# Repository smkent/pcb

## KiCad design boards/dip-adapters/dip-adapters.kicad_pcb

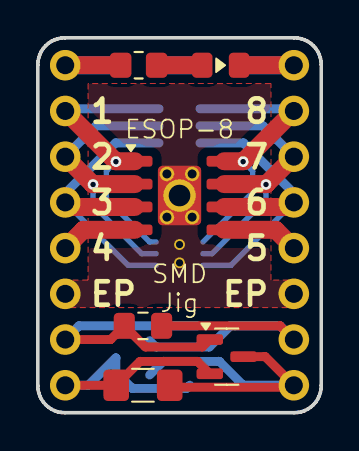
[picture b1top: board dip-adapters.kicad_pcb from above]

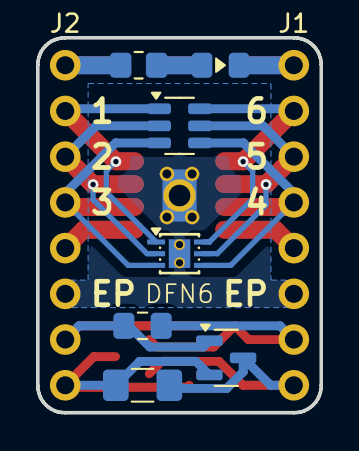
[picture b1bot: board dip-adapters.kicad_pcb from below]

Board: 2 copper layers, 15.7 x 20.8 mm, 15 parts (9 on the bottom side), 17 nets.

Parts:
C1, C2: C; C_0805_2012Metric_Pad1.18x1.45mm_HandSolder
F1, F2: Polyfuse; Fuse_1206_3216Metric_Pad1.42x1.75mm_HandSolder
J1, J2: Conn_01x08; PinHeader_1x08_P2.54mm_Vertical_simple
LED1, LED2: LED; LED_0805_2012Metric_Pad1.15x1.40mm_HandSolder_simple
Q1, Q2: AO3401A; SOT-23
R1, R2: 1K; R_0805_2012Metric_Pad1.20x1.40mm_HandSolder
U1: TP4056; SOIC-8-1EP_3.9x4.9mm_P1.27mm_EP2.41x3.3mm_ThermalVias_Custo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
U2: 1EDN7550B; SOT-23-6
U3: XB6366D; DFN-6_L2.0-W2.0-P0.65-BL-EP_ThermalVias_HandSolder

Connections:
1: J1.2, U1.1 (TEMP), U2.6 (OUT_SNK), U3.6 (VM)
2: J1.3, U1.2 (PROG), U2.5 (OUT_SRC), U3.5 (VM)
3: J1.4, U1.3 (GND), U2.4 (VDD), U3.4 (VM)
4: J1.5, U1.4 (VCC)
5: J2.5, U1.5 (BAT)
6: J2.4, U1.6 (~STDBY), U2.3 (IN+), U3.3 (GND)
7: J2.3, U1.7 (~CHRG), U2.2 (GND), U3.2 (GND)
8: J2.2, U1.8 (CE), U2.1 (IN-), U3.1 (VDD)
EP: J1.6, J2.6, U1.9 (EP), U3.7 (EP)
L7: C1.1, C2.1, J2.7, Q2.1 (G)
L8: F1.1, F2.1, J2.8, Q1.3 (D), Q2.2 (S)
unnamed: J1.1, LED2.1 (K), R2.1
unnamed: J2.1, LED1.1 (K), R1.1
unnamed: LED1.2 (A), R2.2
unnamed: LED2.2 (A), R1.2
R7: C1.2, C2.2, J1.7, Q1.1 (G)
R8: F1.2, F2.2, J1.8, Q1.2 (S), Q2.3 (D)

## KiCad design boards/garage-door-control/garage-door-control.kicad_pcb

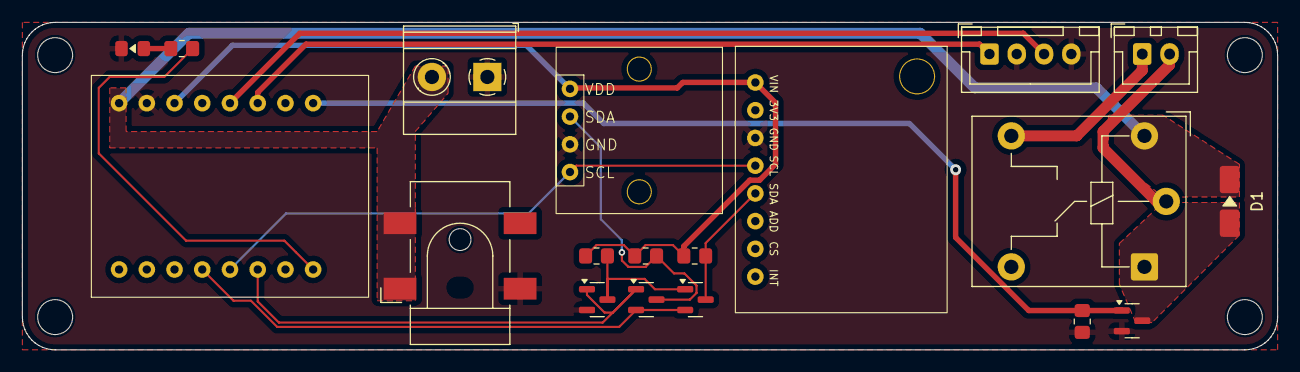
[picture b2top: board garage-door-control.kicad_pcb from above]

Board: 2 copper layers, 115.0 x 30.0 mm, 19 parts (0 on the bottom side), 17 nets.

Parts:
D1: SS34; D_SMA_simple
J1: Barrel_Jack_Switch; BarrelJack_CLIFF_FC681465S_SMT_Horizontal
J2: Conn_01x02; JST_XH_B2B-XH-A_1x02_P2.50mm_Vertical
J3: Conn_01x04_Socket; JST_XH_B4B-XH-A_1x04_P2.50mm_Vertical
J4: Conn_01x02; TerminalBlock_Phoenix_MKDS-1,5-2-5.08_1x02_P5.08mm_Horizont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
K1: Relay_SPDT; Relay_SPDT_Hongfa_HF3F-L-xx-1ZL1T
LED1: LED; LED_0805_2012Metric_Pad1.15x1.40mm_HandSolder_simple
Q1, Q2, Q3, Q4: BSS138; SOT-23
R1, R2, R3, R4, R5: 10K; R_0805_2012Metric_Pad1.20x1.40mm_HandSolder
U1: ESP32-C3-Super-Mini-Pins
U2: AHT20+BMP280
U3: ENS160+AHT2x

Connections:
+3V3: R3.2, R4.2, R5.2, U1.3V3, U2.1 (VDD), U3.1 (VIN)
+5V: D1.1 (K), J1.1, J4.2, K1.A2, U1.5V
BUS0_SDA: Q4.3 (D), R4.1, U2.2 (SDA)
BUS1_SDA: Q3.3 (D), R5.1, U3.5 (SDA)
DOOR_SENSE: J3.3, U1.3
GND: J1.3, J3.2, J3.4, J4.1, LED1.1 (K), Q1.2 (S), Q2.2 (S), R1.1, U1.G (Ground), U2.3 (GND), U3.3 (GND)
LED_STATUS: R2.2, U1.21
LOCK_SENSE: J3.1, U1.2
unnamed: LED1.2 (A), R2.1
unnamed: Q2.3 (D), Q3.1 (G), R3.1
RELAY_COIL: D1.2 (A), K1.A1, Q1.3 (D)
RELAY_CONTROL: Q1.1 (G), R1.2, U1.0
RELAY_SW_COMMON: J2.2, K1.11
RELAY_SW_NO: J2.1, K1.14
SCL: U1.9, U2.4 (SCL), U3.4 (SCL)
SDA: Q3.2 (S), Q4.2 (S), U1.8
SEL: Q2.1 (G), Q4.1 (G), U1.10

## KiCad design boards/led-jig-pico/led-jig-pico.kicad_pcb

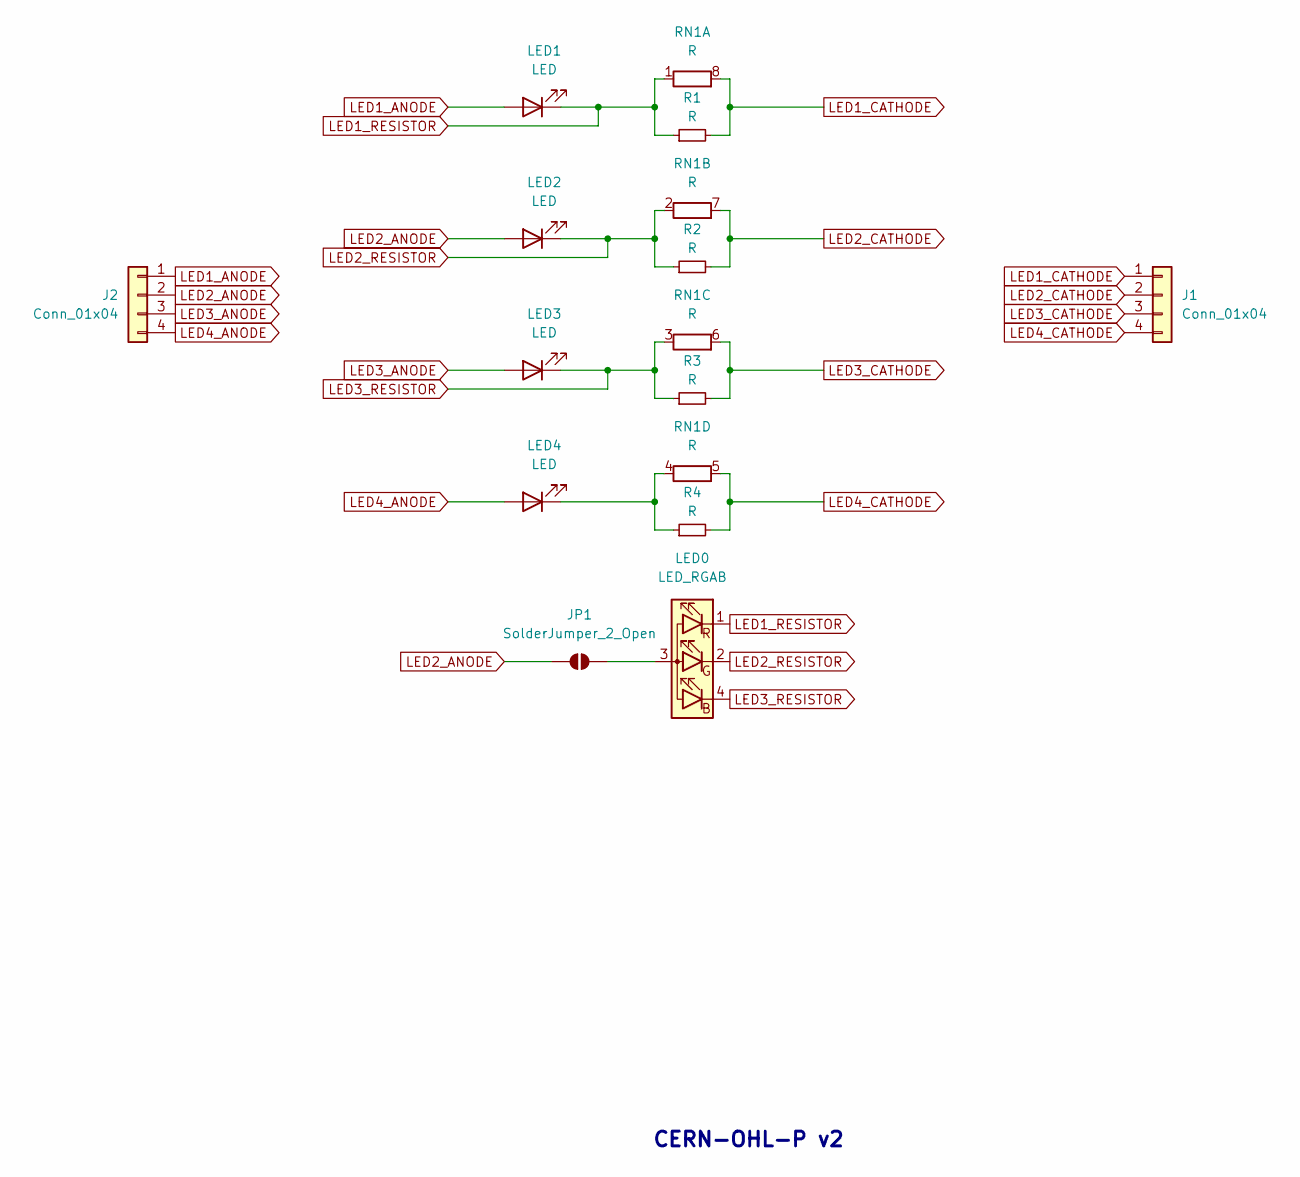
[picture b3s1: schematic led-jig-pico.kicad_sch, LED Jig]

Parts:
J1, J2: Conn_01x04; PinHeader_1x04_P2.54mm_Vertical_simple
JP1: SolderJumper_2_Open; SolderJumper-2_P1.3mm_Open_TrianglePad1.0x1.5mm
LED0: LED_RGAB; LED-ARRAY-SMD_4P-L2.0-W1.3-BR_HandSolder; LCSC Part C965848
LED1, LED2, LED3, LED4: LED; LED_0805_2012Metric_Pad1.15x1.40mm_HandSolder_simple
R1, R2, R3, R4: R; R_0805_2012Metric_Pad1.20x1.40mm_HandSolder
RN1: R; R_Array_Convex_4x0603

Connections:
LED1_ANODE: J2.1, LED1.2 (A)
LED1_CATHODE: J1.1, R1.2, RN1.8 (R1.2)
LED1_RESISTOR: LED0.1 (RK), LED1.1 (K), R1.1, RN1.1 (R1.1)
LED2_ANODE: J2.2, JP1.1 (A), LED2.2 (A)
LED2_CATHODE: J1.2, R2.2, RN1.7 (R2.2)
LED2_RESISTOR: LED0.2 (GK), LED2.1 (K), R2.1, RN1.2 (R2.1)
LED3_ANODE: J2.3, LED3.2 (A)
LED3_CATHODE: J1.3, R3.2, RN1.6 (R3.2)
LED3_RESISTOR: LED0.4 (BK), LED3.1 (K), R3.1, RN1.3 (R3.1)
LED4_ANODE: J2.4, LED4.2 (A)
LED4_CATHODE: J1.4, R4.2, RN1.5 (R4.2)
unnamed: JP1.2 (B), LED0.3 (A)
unnamed: LED4.1 (K), R4.1, RN1.4 (R4.1)

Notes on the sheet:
CERN-OHL-P v2

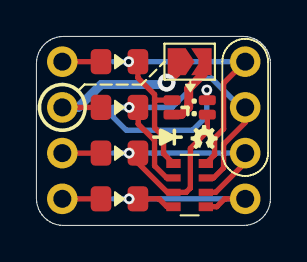
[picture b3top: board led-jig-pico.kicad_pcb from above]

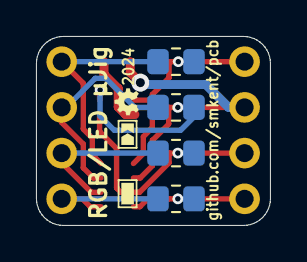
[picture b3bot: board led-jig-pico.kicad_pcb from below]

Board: 2 copper layers, 13.0 x 10.5 mm, 13 parts (6 on the bottom side), 13 nets.

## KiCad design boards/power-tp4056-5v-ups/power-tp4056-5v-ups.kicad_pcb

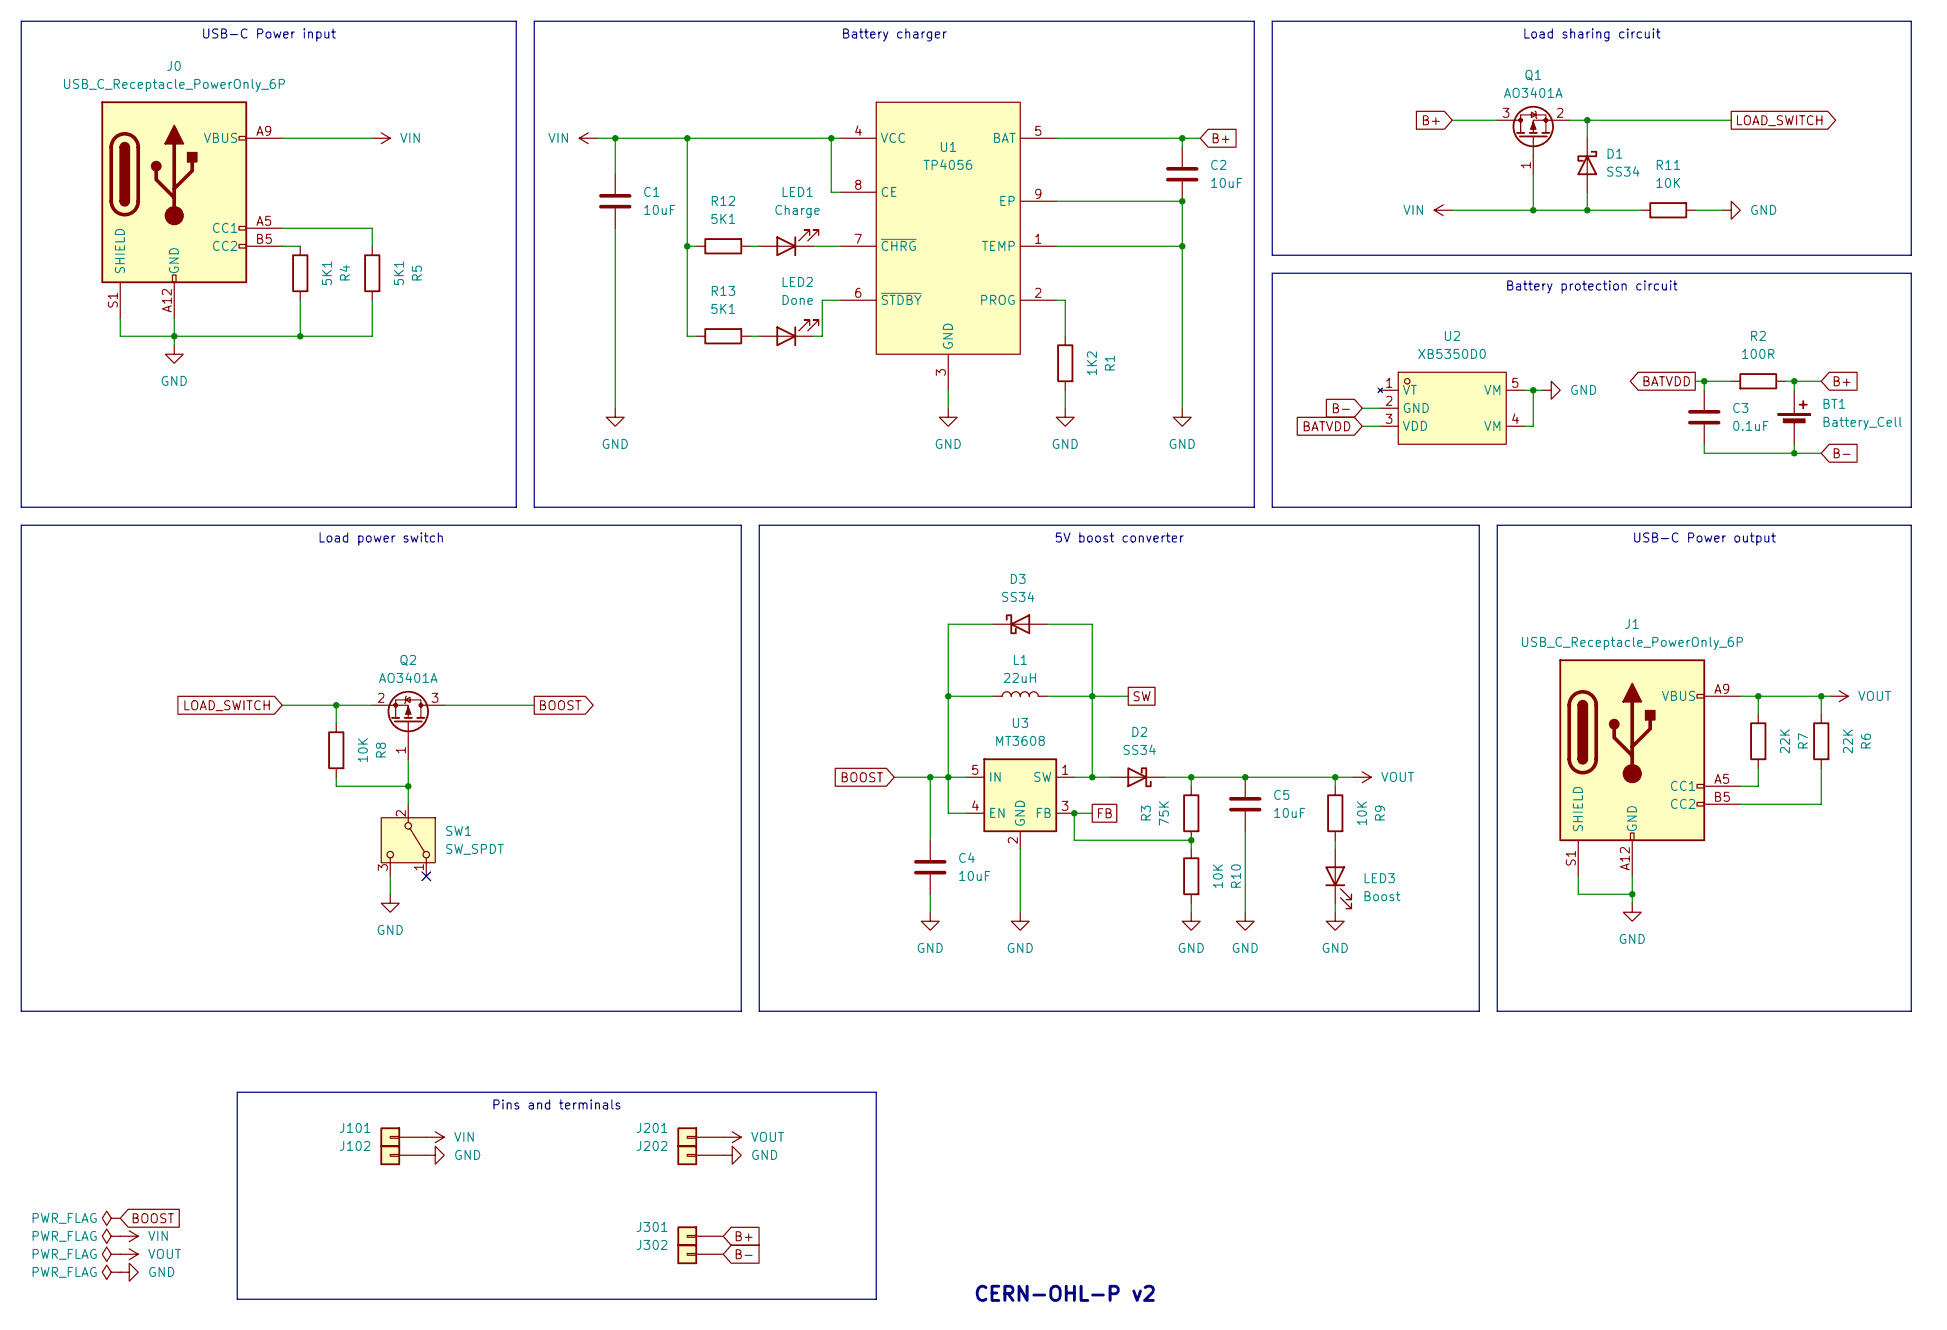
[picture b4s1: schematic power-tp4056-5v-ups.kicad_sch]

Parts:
BT1: Battery_Cell; JST_XH_B2B-XH-A_1x02_P2.50mm_Vertical_simple_pad2gnd
C1, C2, C4: 10uF; C_0603_1608Metric; LCSC Part C19702
C3: 0.1uF; C_0402_1005Metric; LCSC Part C1525
C5: 10uF; C_0402_1005Metric; LCSC Part C15525
D1, D2, D3: SS34; D_SMA_simple; LCSC Part C8678
J0, J1: USB_C_Receptacle_PowerOnly_6P; USB_C_Receptacle_GCT_USB4125-xx-x_6P_TopMnt_Horizontal_hand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
J101, J201, J301: Conn_01x01; PinHeader_1x01_P2.54mm_simple
J102, J202, J302: Conn_01x01; PinHeader_1x01_P2.54mm_simple_square
L1: 22uH; IND-SMD_L7.0-W6.6; LCSC Part C5832376
LED1: Charge; LED_0805_2012Metric_Pad1.15x1.40mm_HandSolder_simple
LED2: Done; LED_0805_2012Metric_Pad1.15x1.40mm_HandSolder_simple
LED3: Boost; LED_0805_2012Metric_Pad1.15x1.40mm_HandSolder_simple
Q1, Q2: AO3401A; SOT-23; LCSC Part C15127
R1: 1K2; R_0805_2012Metric_Pad1.20x1.40mm_HandSolder; LCSC Part C17379
R2: 100R; R_0805_2012Metric_Pad1.20x1.40mm_HandSolder; LCSC Part C17408
R3: 75K; R_0402_1005Metric; LCSC Part C25798
R4, R5, R12, R13: 5K1; R_0402_1005Metric; LCSC Part C25905
R6, R7: 22K; R_0402_1005Metric; LCSC Part C25768
R8, R9, R10, R11: 10K; R_0402_1005Metric; LCSC Part C25744
SW1: SW_SPDT; SW-TH_DEALON_SS-12D01-GX_simple; LCSC Part C2998803
U1: TP4056; SOIC-8-1EP_3.9x4.9mm_P1.27mm_EP2.41x3.3mm_ThermalVias_Custo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; JLCPCB_CORRECTION 0; 0; 270
U2: XB5350D0; SOT-23-5_simple; JLCPCB_CORRECTION 0; 0; 180
U3: MT3608; SOT-23-6; LCSC Part C84817

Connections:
B+: BT1.1 (+), C2.2, J301.1, Q1.3 (D), R2.1, U1.5 (BAT)
B-: BT1.2 (-), C3.1, J302.1, U2.2 (GND)
BATVDD: C3.2, R2.2, U2.3 (VDD)
BOOST: C4.1, D3.1 (K), L1.1, Q2.3 (D), U3.4 (EN), U3.5 (IN)
FB: R3.2, R10.1, U3.3 (FB)
GND: C1.2, C2.1, C4.2, C5.2, J0.A12 (GND), J0.B12 (GND), J0.S1 (SHIELD), J1.A12 (GND), J1.B12 (GND), J1.S1 (SHIELD), J102.1, J202.1, LED3.1 (K), R1.2, R4.2, R5.2, R10.2, R11.2, SW1.3 (C), U1.1 (TEMP), U1.3 (GND), U1.9 (EP), U2.4 (VM), U2.5 (VM), U3.2 (GND)
LOAD_SWITCH: D1.1 (K), Q1.2 (S), Q2.2 (S), R8.1
unnamed: J0.A5 (CC1), R5.1
unnamed: J0.B5 (CC2), R4.1
unnamed: J1.A5 (CC1), R7.2
unnamed: J1.B5 (CC2), R6.2
unnamed: LED1.2 (A), R12.2
unnamed: LED1.1 (K), U1.7 (~CHRG)
unnamed: LED2.2 (A), R13.2
unnamed: LED2.1 (K), U1.6 (~STDBY)
unnamed: LED3.2 (A), R9.2
unnamed: Q2.1 (G), R8.2, SW1.2 (B)
unnamed: R1.1, U1.2 (PROG)
SW: D2.2 (A), D3.2 (A), L1.2, U3.1 (SW)
VIN: C1.1, D1.2 (A), J0.A9 (VBUS), J0.B9 (VBUS), J101.1, Q1.1 (G), R11.1, R12.1, R13.1, U1.4 (VCC), U1.8 (CE)
VOUT: C5.1, D2.1 (K), J1.A9 (VBUS), J1.B9 (VBUS), J201.1, R3.1, R6.1, R7.1, R9.1

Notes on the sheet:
Pins and terminals
Battery protection circuit
USB-C Power output
USB-C Power input
Load sharing circuit
Load power switch
Battery charger
5V boost converter
CERN-OHL-P v2

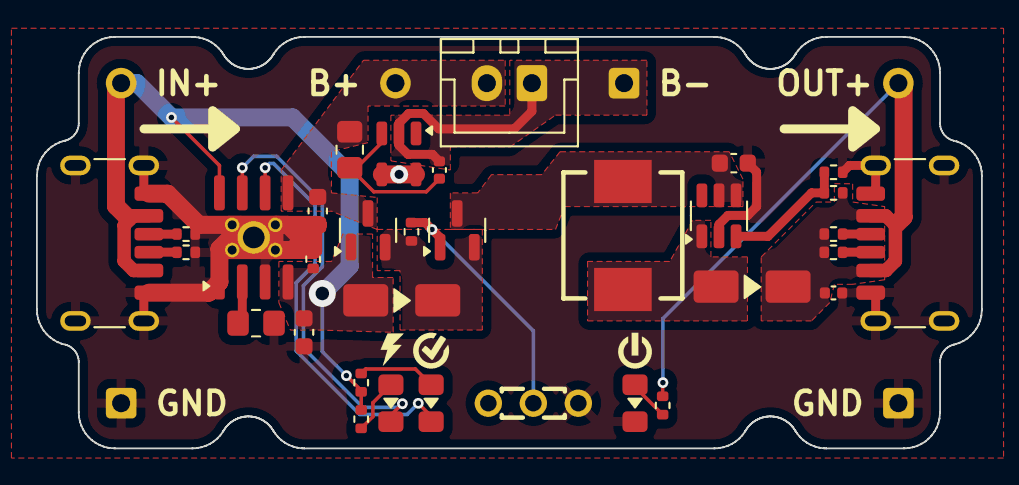
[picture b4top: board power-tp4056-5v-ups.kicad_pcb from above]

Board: 2 copper layers, 52.5 x 22.9 mm, 39 parts (0 on the bottom side), 21 nets.

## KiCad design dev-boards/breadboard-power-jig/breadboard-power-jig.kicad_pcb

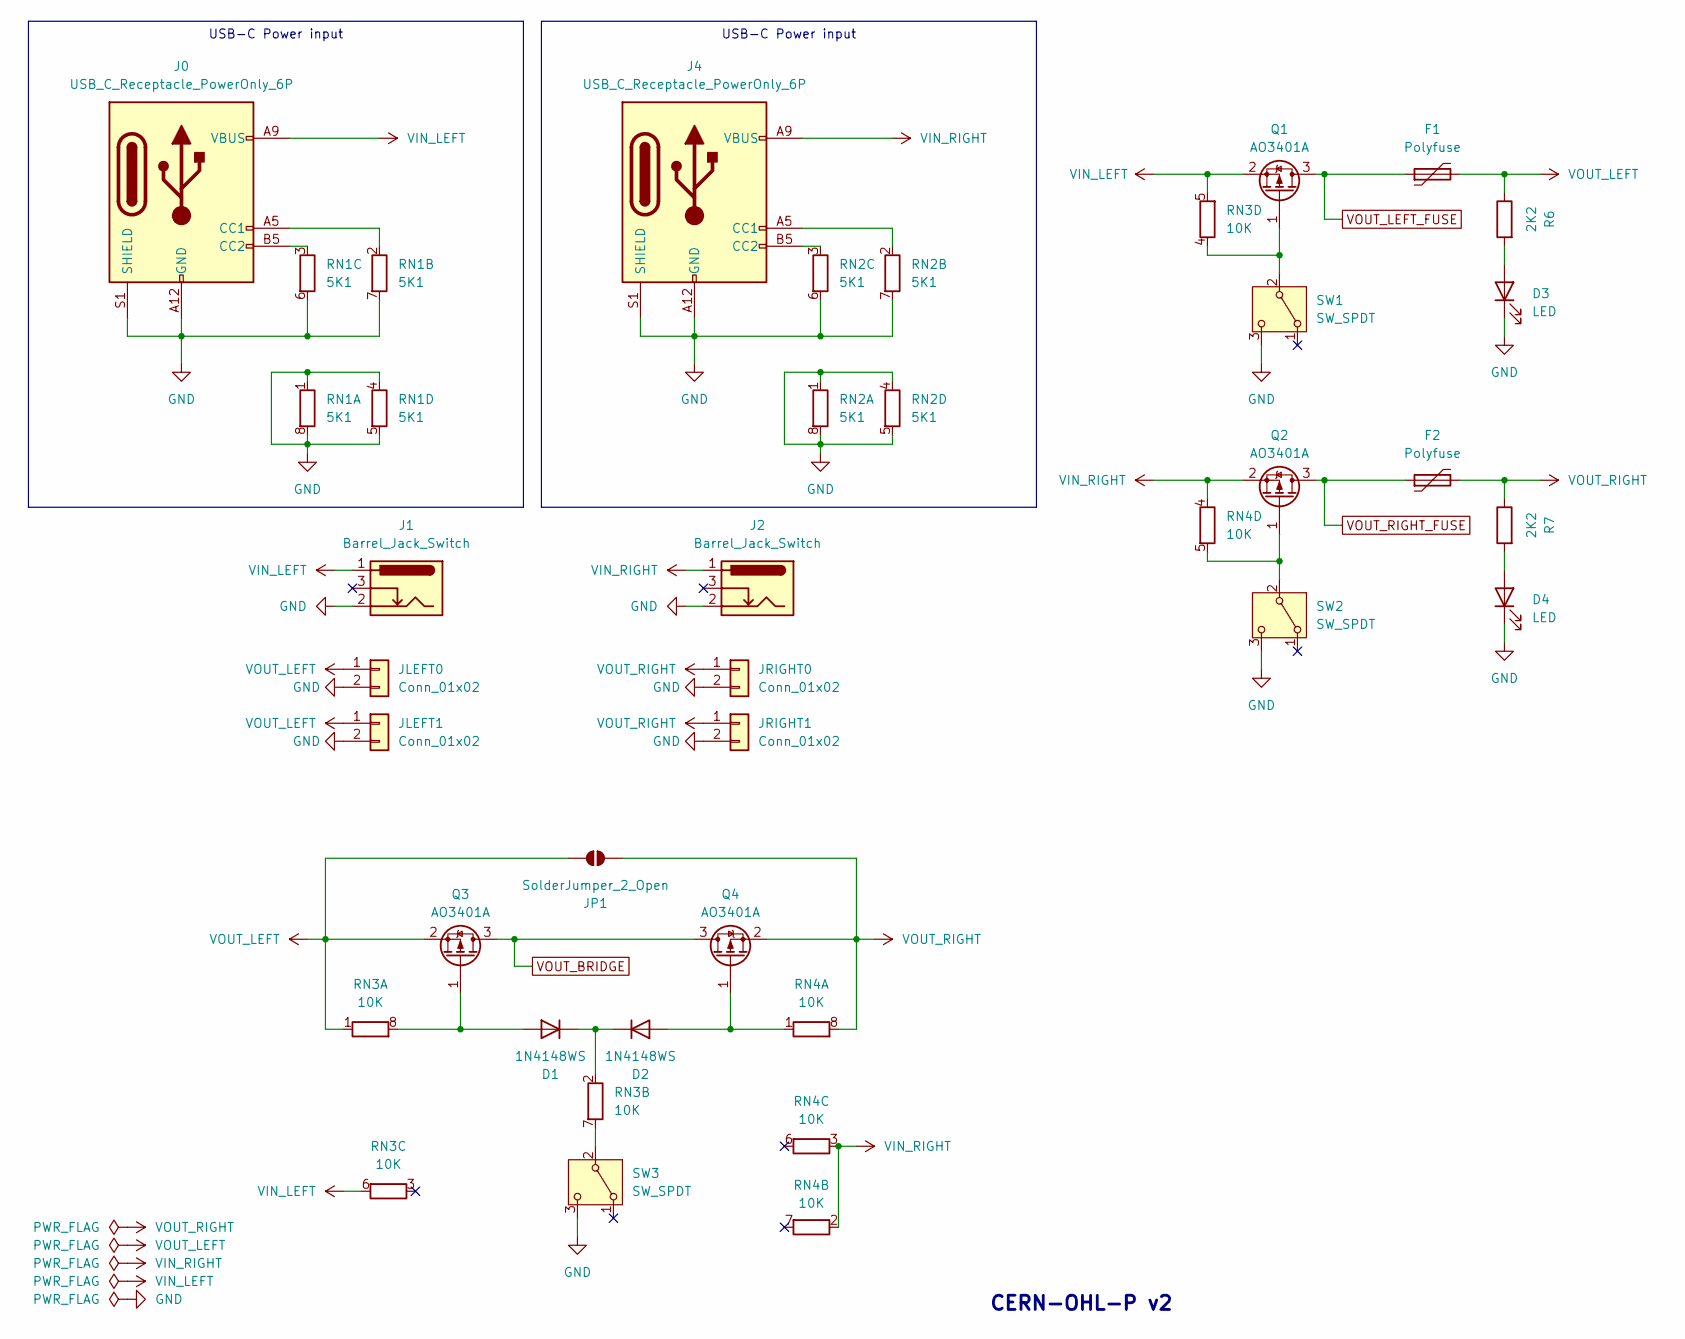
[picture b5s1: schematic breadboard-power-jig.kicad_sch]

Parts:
D1, D2: 1N4148WS; D_SOD-323_HandSoldering_simple
D3, D4: LED; LED_0805_2012Metric_Pad1.15x1.40mm_HandSolder_simple
F1, F2: Polyfuse; Fuse_1206_3216Metric_Pad1.42x1.75mm_HandSolder_simple
J0, J4: USB_C_Receptacle_PowerOnly_6P; USB_C_Receptacle_GCT_USB4125-xx-x_6P_TopMnt_Horizontal_hand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
J1, J2: Barrel_Jack_Switch; Conn_Combo_DC-050_TerminalBlock_JST-XH-2P-horizontal-TH-or-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
JLEFT0, JLEFT1: Conn_01x02; PinHeader_1x02_P2.54mm_Vertical_simple_pad2gnd
JP1: SolderJumper_2_Open; SolderJumper-2_P1.3mm_Open_RoundedPad1.0x1.5mm_simple
JRIGHT0, JRIGHT1: Conn_01x02; PinHeader_1x02_P2.54mm_Vertical_simple_pad2gnd
Q1, Q2, Q3, Q4: AO3401A; SOT-23; LCSC Part C15127
R6, R7: 2K2; R_0805_2012Metric_Pad1.20x1.40mm_HandSolder
RN1, RN2: 5K1; R_Array_Convex_4x0603
RN3, RN4: 10K; R_Array_Convex_4x0603
SW1, SW2: SW_SPDT; SW-TH_DEALON_SS-12D01-GX_simple; LCSC Part C2998803
SW3: SW_SPDT; SW-SMD_3P-P1.50_L2.7-W6.6; LCSC Part C2998803

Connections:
GND: D3.1 (K), D4.1 (K), J0.A12 (GND), J0.B12 (GND), J0.S1 (SHIELD), J1.2, J2.2, J4.A12 (GND), J4.B12 (GND), J4.S1 (SHIELD), JLEFT0.2, JLEFT1.2, JRIGHT0.2, JRIGHT1.2, RN1.1 (R1.1), RN1.4 (R4.1), RN1.5 (R4.2), RN1.6 (R3.2), RN1.7 (R2.2), RN1.8 (R1.2), RN2.1 (R1.1), RN2.4 (R4.1), RN2.5 (R4.2), RN2.6 (R3.2), RN2.7 (R2.2), RN2.8 (R1.2), SW1.3 (C), SW2.3 (C), SW3.3 (C)
unnamed: D1.2 (A), Q3.1 (G), RN3.8 (R1.2)
unnamed: D1.1 (K), D2.1 (K), RN3.2 (R2.1)
unnamed: D2.2 (A), Q4.1 (G), RN4.1 (R1.1)
unnamed: D3.2 (A), R6.2
unnamed: D4.2 (A), R7.2
unnamed: J0.A5 (CC1), RN1.2 (R2.1)
unnamed: J0.B5 (CC2), RN1.3 (R3.1)
unnamed: J4.A5 (CC1), RN2.2 (R2.1)
unnamed: J4.B5 (CC2), RN2.3 (R3.1)
unnamed: Q1.1 (G), RN3.4 (R4.1), SW1.2 (B)
unnamed: Q2.1 (G), RN4.5 (R4.2), SW2.2 (B)
unnamed: RN3.7 (R2.2), SW3.2 (B)
VIN_LEFT: J0.A9 (VBUS), J0.B9 (VBUS), J1.1, Q1.2 (S), RN3.5 (R4.2), RN3.6 (R3.2)
VIN_RIGHT: J2.1, J4.A9 (VBUS), J4.B9 (VBUS), Q2.2 (S), RN4.2 (R2.1), RN4.3 (R3.1), RN4.4 (R4.1)
VOUT_BRIDGE: Q3.3 (D), Q4.3 (D)
VOUT_LEFT: F1.2, JLEFT0.1, JLEFT1.1, JP1.1 (A), Q3.2 (S), R6.1, RN3.1 (R1.1)
VOUT_LEFT_FUSE: F1.1, Q1.3 (D)
VOUT_RIGHT: F2.2, JP1.2 (B), JRIGHT0.1, JRIGHT1.1, Q4.2 (S), R7.1, RN4.8 (R1.2)
VOUT_RIGHT_FUSE: F2.1, Q2.3 (D)

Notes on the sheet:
USB-C Power input
CERN-OHL-P v2

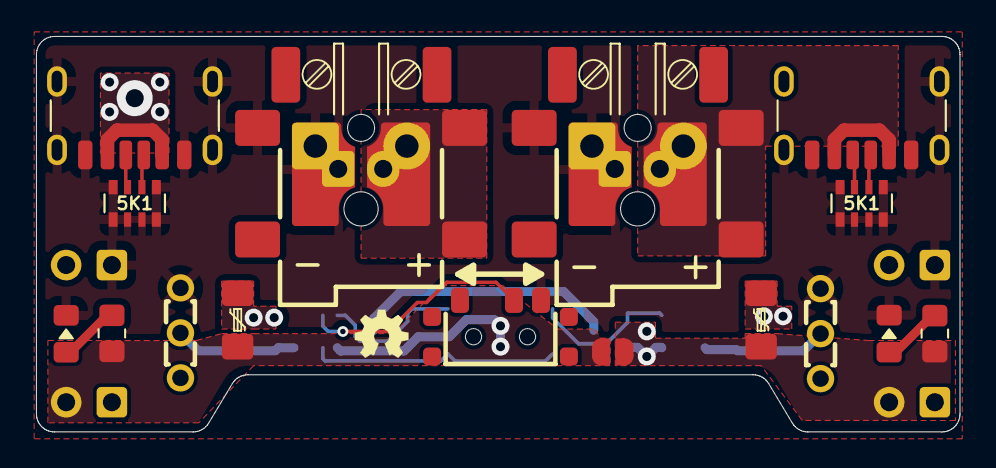
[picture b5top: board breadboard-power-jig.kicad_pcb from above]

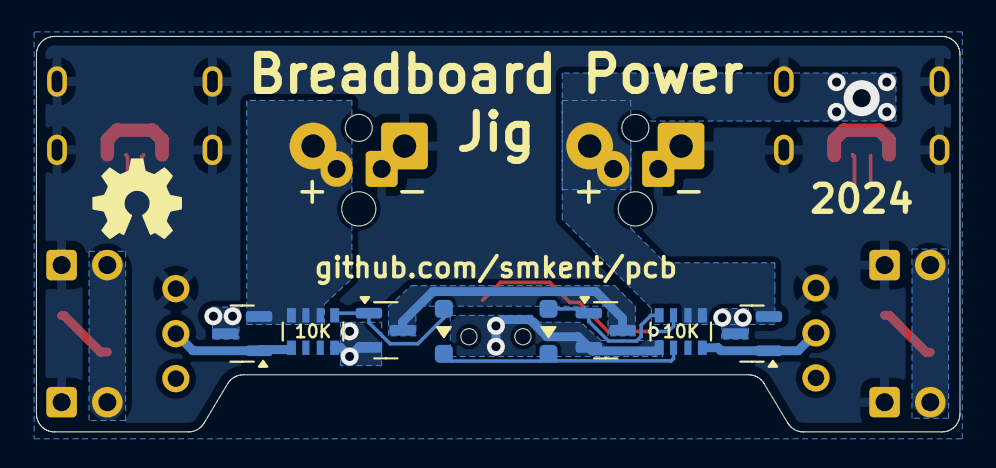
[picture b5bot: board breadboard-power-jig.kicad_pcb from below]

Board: 2 copper layers, 51.3 x 22.0 mm, 28 parts (12 on the bottom side), 20 nets.

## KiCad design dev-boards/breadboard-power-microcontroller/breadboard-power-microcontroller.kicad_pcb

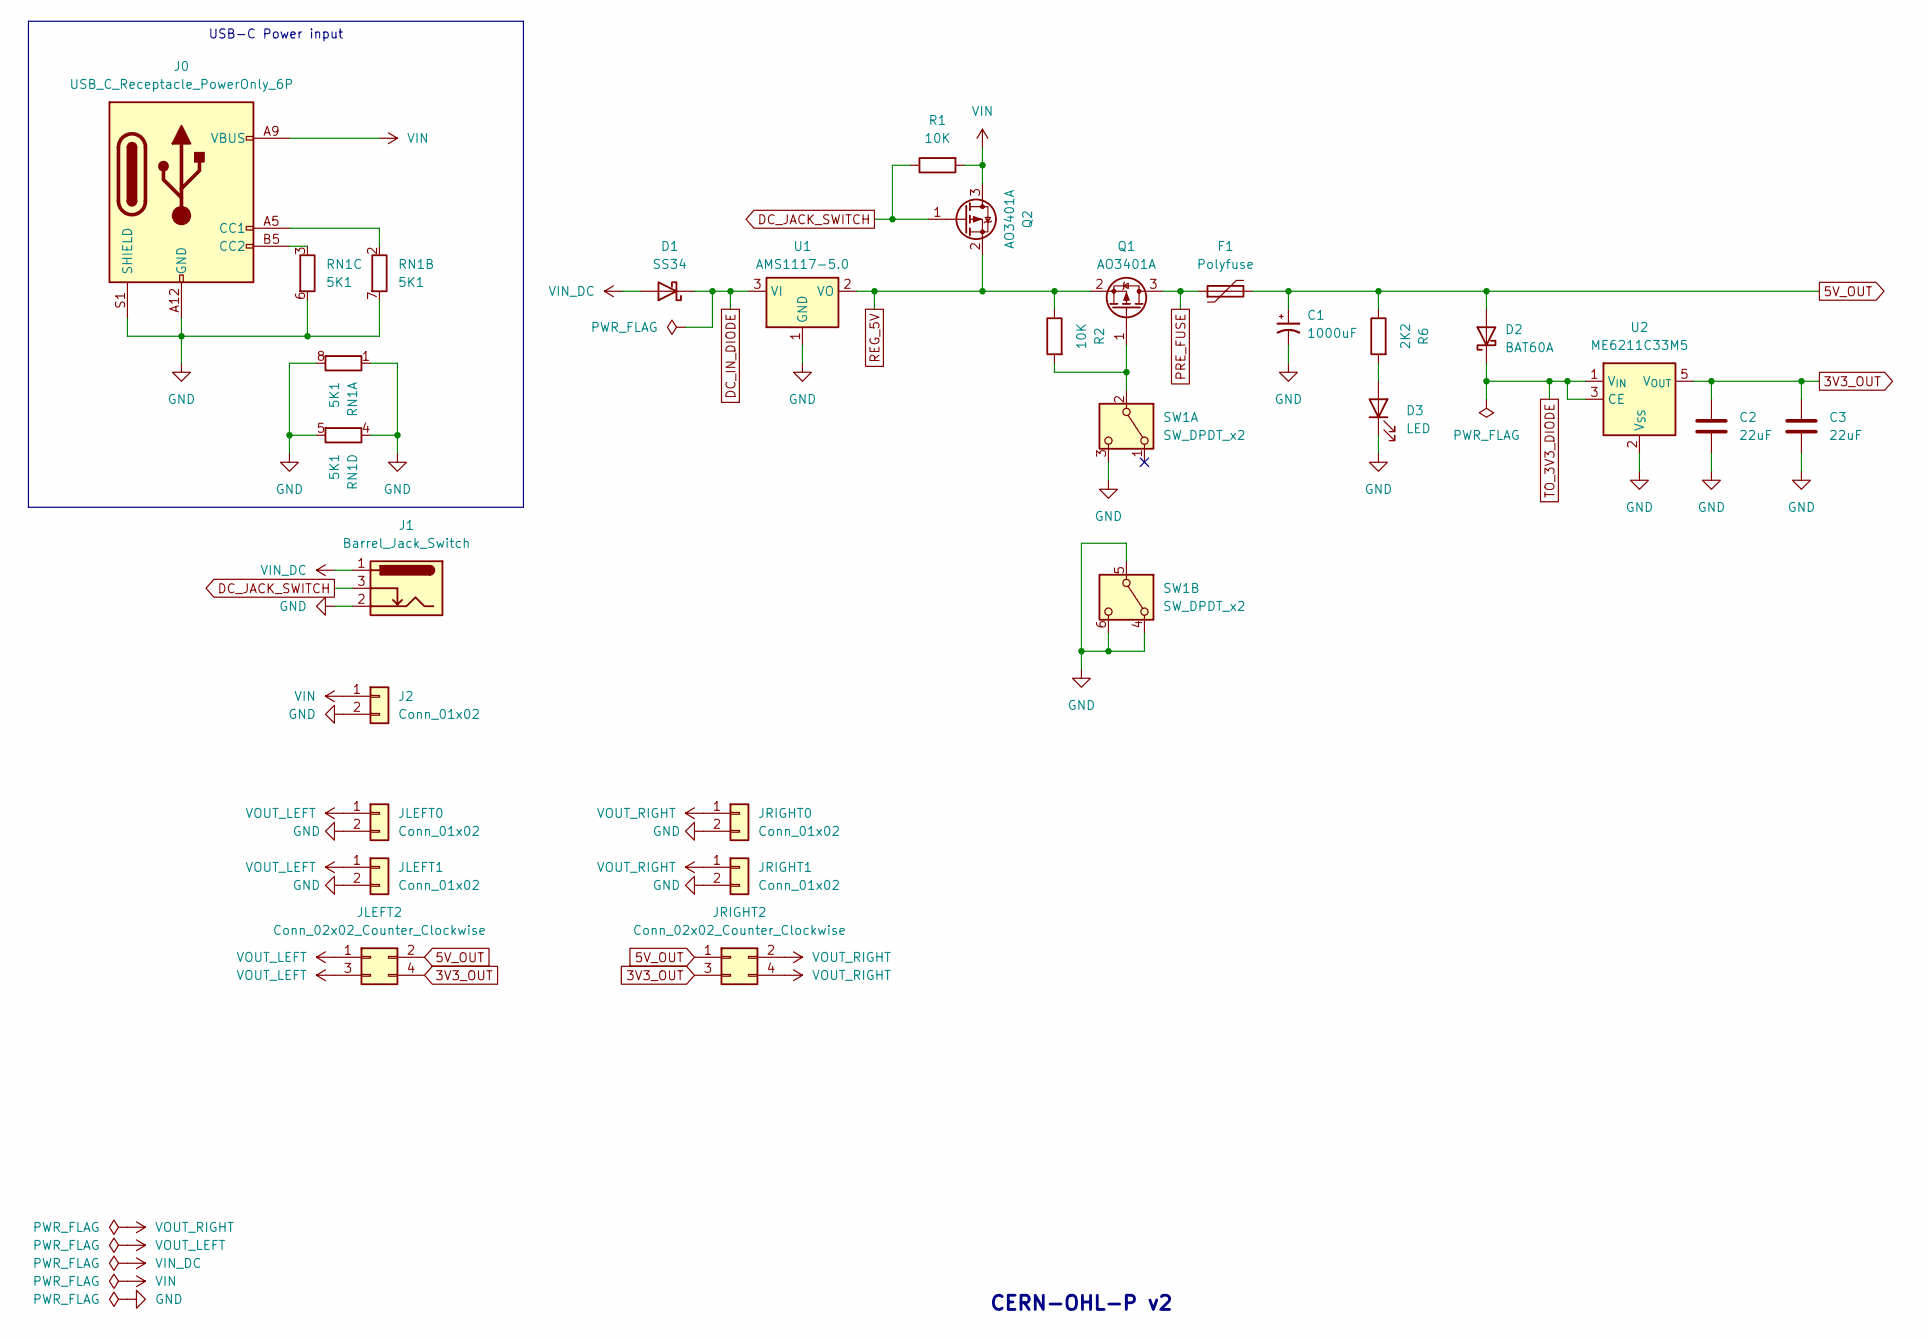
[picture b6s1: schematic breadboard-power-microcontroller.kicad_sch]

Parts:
C1: 1000uF; CP_Elec_8x10.5
C2, C3: 22uF; C_0805_2012Metric_Pad1.18x1.45mm_HandSolder
D1: SS34; D_SMA_simple
D2: BAT60A; D_SOD-323_HandSoldering_simple
D3: LED; LED_0805_2012Metric_Pad1.15x1.40mm_HandSolder_simple
F1: Polyfuse; Fuse_1206_3216Metric_Pad1.42x1.75mm_HandSolder_simple
J0: USB_C_Receptacle_PowerOnly_6P; USB_C_Receptacle_GCT_USB4125-xx-x_6P_TopMnt_Horizontal_hand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
J1: Barrel_Jack_Switch; DC-IN_DC-050-2.0-BB_rev2
J2: Conn_01x02; JST_XH_S2B-XH-2AW_1x02_P2.50mm_TH-or-SMD_pad2gnd_trim
JLEFT0, JLEFT1: Conn_01x02; PinHeader_1x02_P2.54mm_Vertical_simple_pad2gnd
JLEFT2: Conn_02x02_Counter_Clockwise; PinHeader_2x02_P2.54mm_Vertical_simple
JRIGHT0, JRIGHT1: Conn_01x02; PinHeader_1x02_P2.54mm_Vertical_simple_pad2gnd
JRIGHT2: Conn_02x02_Counter_Clockwise; PinHeader_2x02_P2.54mm_Vertical_simple
Q1, Q2: AO3401A; SOT-23; LCSC Part C15127
R1, R2: 10K; R_0805_2012Metric_Pad1.20x1.40mm_HandSolder
R6: 2K2; R_0805_2012Metric_Pad1.20x1.40mm_HandSolder
RN1: 5K1; R_Array_Convex_4x0603
SW1: SW_DPDT_x2; SW-TH_6P-L7.0-W7.0-P2.00_90deg
U1: AMS1117-5.0; SOT-223-3_TabPin2
U2: ME6211C33M5; SOT-23-5_HandSoldering_simple

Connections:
3V3_OUT: C2.1, C3.1, JLEFT2.4, JRIGHT2.3, U2.5 (V_{OUT})
5V_OUT: C1.1, D2.2 (A), F1.2, JLEFT2.2, JRIGHT2.1, R6.1
DC_IN_DIODE: D1.1 (K), U1.3 (VI)
DC_JACK_SWITCH: J1.3, Q2.1 (G), R1.1
GND: C1.2, C2.2, C3.2, D3.1 (K), J0.A12 (GND), J0.B12 (GND), J0.S1 (SHIELD), J1.2, J2.2, JLEFT0.2, JLEFT1.2, JRIGHT0.2, JRIGHT1.2, RN1.1 (R1.1), RN1.4 (R4.1), RN1.5 (R4.2), RN1.6 (R3.2), RN1.7 (R2.2), RN1.8 (R1.2), SW1.3 (C), SW1.4 (A), SW1.5 (B), SW1.6 (C), U1.1 (GND), U2.2 (V_{SS})
unnamed: D3.2 (A), R6.2
unnamed: J0.A5 (CC1), RN1.2 (R2.1)
unnamed: J0.B5 (CC2), RN1.3 (R3.1)
unnamed: Q1.1 (G), R2.2, SW1.2 (B)
PRE_FUSE: F1.1, Q1.3 (D)
REG_5V: Q1.2 (S), Q2.2 (S), R2.1, U1.2 (VO)
TO_3V3_DIODE: D2.1 (K), U2.1 (V_{IN}), U2.3 (CE)
VIN: J0.A9 (VBUS), J0.B9 (VBUS), J2.1, Q2.3 (D), R1.2
VIN_DC: D1.2 (A), J1.1
VOUT_LEFT: JLEFT0.1, JLEFT1.1, JLEFT2.1, JLEFT2.3
VOUT_RIGHT: JRIGHT0.1, JRIGHT1.1, JRIGHT2.2, JRIGHT2.4

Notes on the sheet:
USB-C Power input
CERN-OHL-P v2

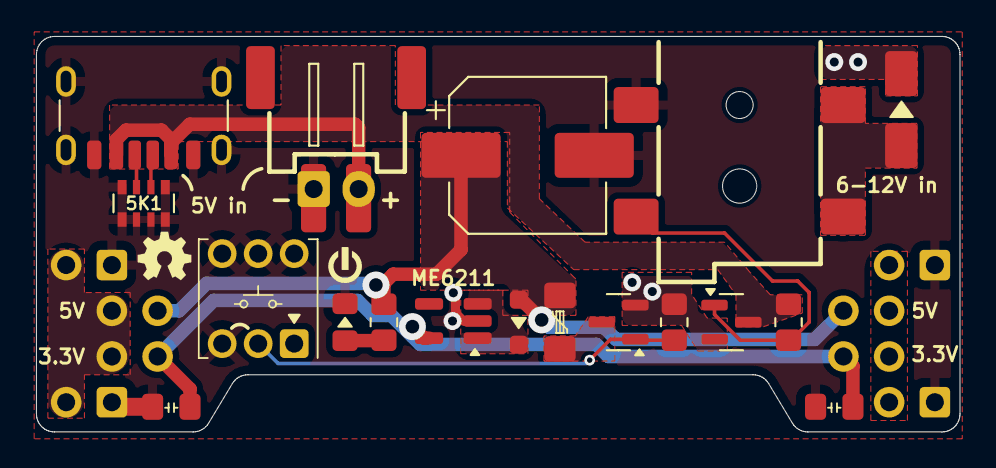
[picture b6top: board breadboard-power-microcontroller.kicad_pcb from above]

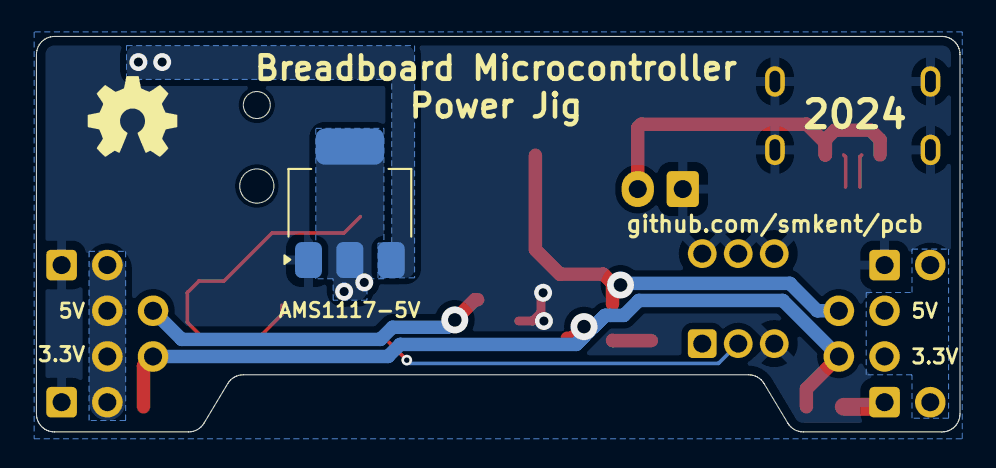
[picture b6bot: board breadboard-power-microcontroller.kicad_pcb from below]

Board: 2 copper layers, 51.3 x 22.0 mm, 25 parts (5 on the bottom side), 16 nets.
